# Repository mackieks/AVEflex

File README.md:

# AVEflex

FPC for relocating the Nintendo Wii AVE, licensed under Solderpad Hardware License v2.1. Original design from 2020, updated 2023

Repo contains EAGLE and KiCAD 8 source files, gerbers for manufacture, and an iBOM file.

Mouser project with the passive components is available [here](https://www.mouser.com/ProjectManager/ProjectDetail.aspx?AccessID=5053a6b78b).

Details and install notes at https://bitbuilt.net/forums/index.php?threads/fs-aveflex-wii-ave-relocation-fpc.3884/

## Gallery

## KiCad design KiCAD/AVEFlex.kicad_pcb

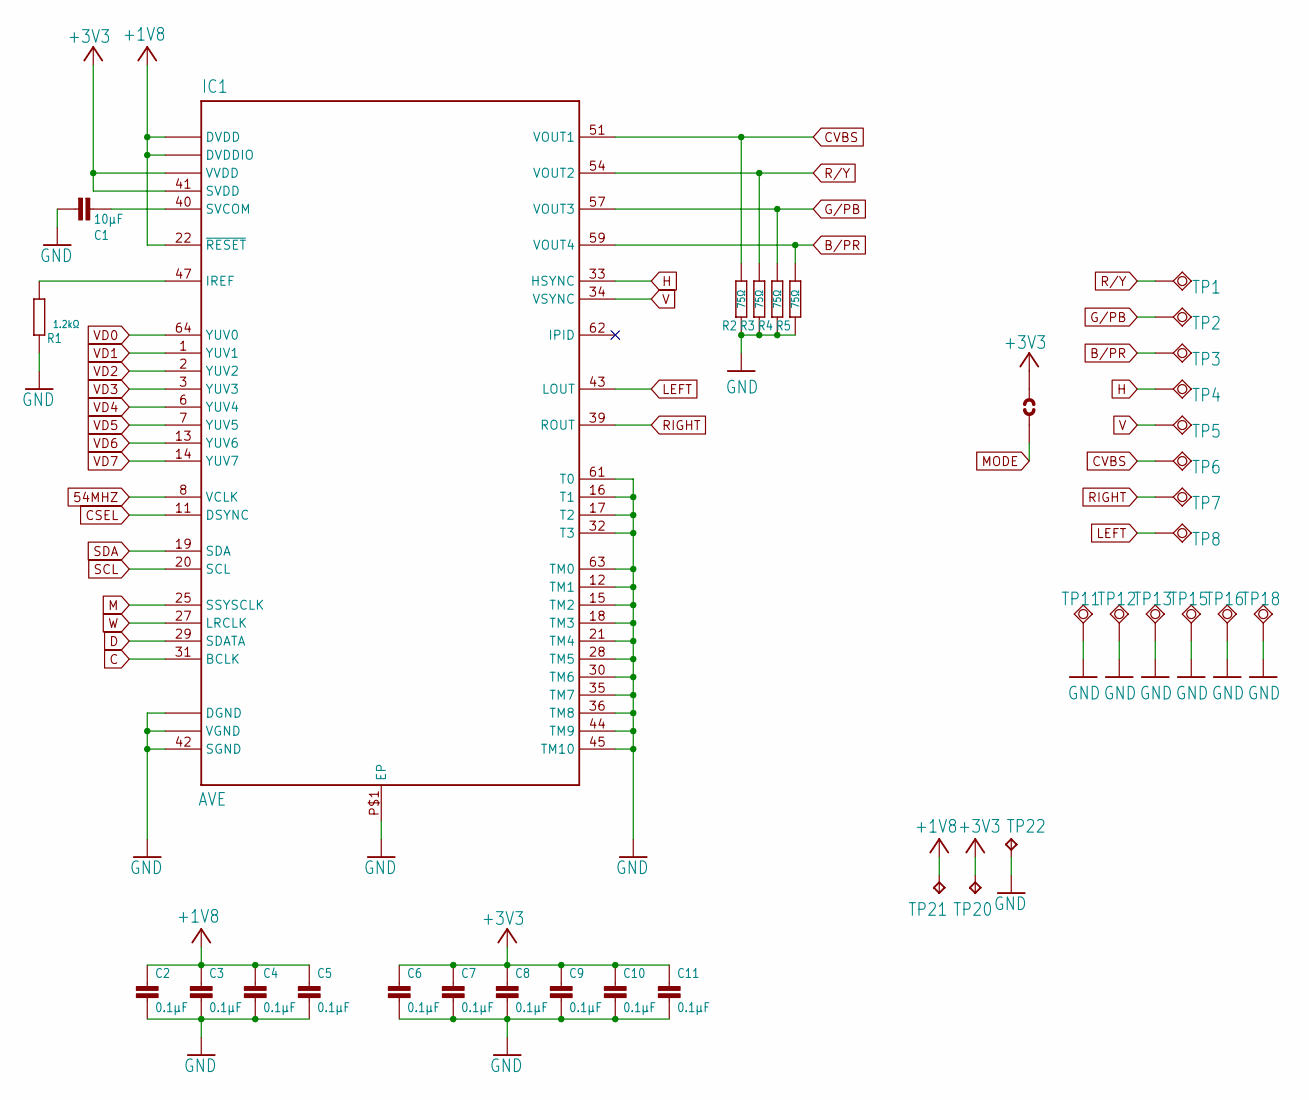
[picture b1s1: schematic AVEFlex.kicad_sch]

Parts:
C1: 10µF; C0603
C2, C3, C4, C5, C6, C7, C8, C9, C10, C11: 0.1µF; C0402
IC1: AVE; TQFP64-10X10
JP1: JUMPER-SMT_2_NO_SILK; SMT-JUMPER_2_NO_SILK
R1: 1.2kΩ; R0402
R2, R3, R4, R5: 75Ω; R0402
TP1, TP2, TP3, TP4, TP5, TP6, TP7, TP8, TP11, TP12, TP13, TP15, TP16, TP18: TPSQTP10R; TP10R
TP20, TP21, TP22: TPTP10SQ; TP10SQ

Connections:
54MHZ: IC1.8 (VCLK)
+1V8: C2.1, C3.1, C4.1, C5.1, IC1.4 (DVDDIO), IC1.9 (DVDD), IC1.22 (~RESET), IC1.23 (DVDD), IC1.26 (DVDDIO), TP21.TP
+3V3: C6.1, C7.1, C8.1, C9.1, C10.1, C11.1, IC1.37 (VVDD), IC1.41 (SVDD), IC1.46 (VVDD), IC1.50 (VVDD), IC1.53 (VVDD), IC1.56 (VVDD), IC1.60 (VVDD), JP1.2, TP20.TP
B/PR: IC1.59 (VOUT4), R5.1, TP3.TP
C: IC1.31 (BCLK)
CSEL: IC1.11 (DSYNC)
CVBS: IC1.51 (VOUT1), R2.1, TP6.TP
D: IC1.29 (SDATA)
GND: C1.2, C2.2, C3.2, C4.2, C5.2, C6.2, C7.2, C8.2, C9.2, C10.2, C11.2, IC1.5 (DGND), IC1.10 (DGND), IC1.12 (TM1), IC1.15 (TM2), IC1.16 (T1), IC1.17 (T2), IC1.18 (TM3), IC1.21 (TM4), IC1.24 (DGND), IC1.28 (TM5), IC1.30 (TM6), IC1.32 (T3), IC1.35 (TM7), IC1.36 (TM8), IC1.38 (VGND), IC1.42 (SGND), IC1.44 (TM9), IC1.45 (TM10), IC1.48 (VGND), IC1.49 (VGND), IC1.52 (VGND), IC1.55 (VGND), IC1.58 (VGND), IC1.61 (T0), IC1.63 (TM0), IC1.P$1 (EP), R1.2, R2.2, R3.2, R4.2, R5.2, TP11.TP, TP12.TP, TP13.TP, TP15.TP, TP16.TP, TP18.TP, TP22.TP
G/PB: IC1.57 (VOUT3), R4.1, TP2.TP
H: IC1.33 (HSYNC), TP4.TP
LEFT: IC1.43 (LOUT), TP8.TP
M: IC1.25 (SSYSCLK)
MODE: JP1.1
unnamed: IC1.47 (IREF), R1.1
unnamed: C1.1, IC1.40 (SVCOM)
RIGHT: IC1.39 (ROUT), TP7.TP
R/Y: IC1.54 (VOUT2), R3.1, TP1.TP
SCL: IC1.20 (SCL)
SDA: IC1.19 (SDA)
V: IC1.34 (VSYNC), TP5.TP
VD0: IC1.64 (YUV0)
VD1: IC1.1 (YUV1)
VD2: IC1.2 (YUV2)
VD3: IC1.3 (YUV3)
VD4: IC1.6 (YUV4)
VD5: IC1.7 (YUV5)
VD6: IC1.13 (YUV6)
VD7: IC1.14 (YUV7)
W: IC1.27 (LRCLK)

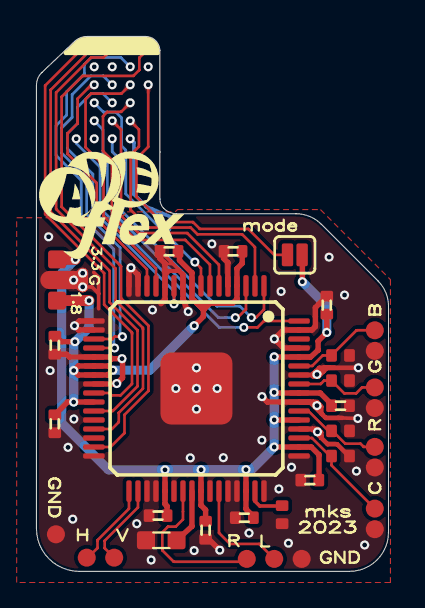
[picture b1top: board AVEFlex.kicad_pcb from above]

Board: 2 copper layers, 19.6 x 29.7 mm, 35 parts (0 on the bottom side), 13 nets.

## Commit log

2023-06-16 Rename AVEFlex.sch to EAGLE/AVEFlex.sch
2023-06-16 Rename AVEFlex.brd to EAGLE/AVEFlex.brd
2023-06-17 Create LICENSE.txt
    Add TAPR Open Hardware License
2023-12-20 fix ibom, add schematic image
2023-12-20 move schematic.png
2024-01-23 update to solderpad permissive license
2024-03-17 Partial port to KiCad, fix of edge cuts
2024-03-17 Minor silkscreen fixes
2024-03-17 Update KiCAD version
    - updated KiCAD version
    - updated Gerbers
    - added new iBOM file
